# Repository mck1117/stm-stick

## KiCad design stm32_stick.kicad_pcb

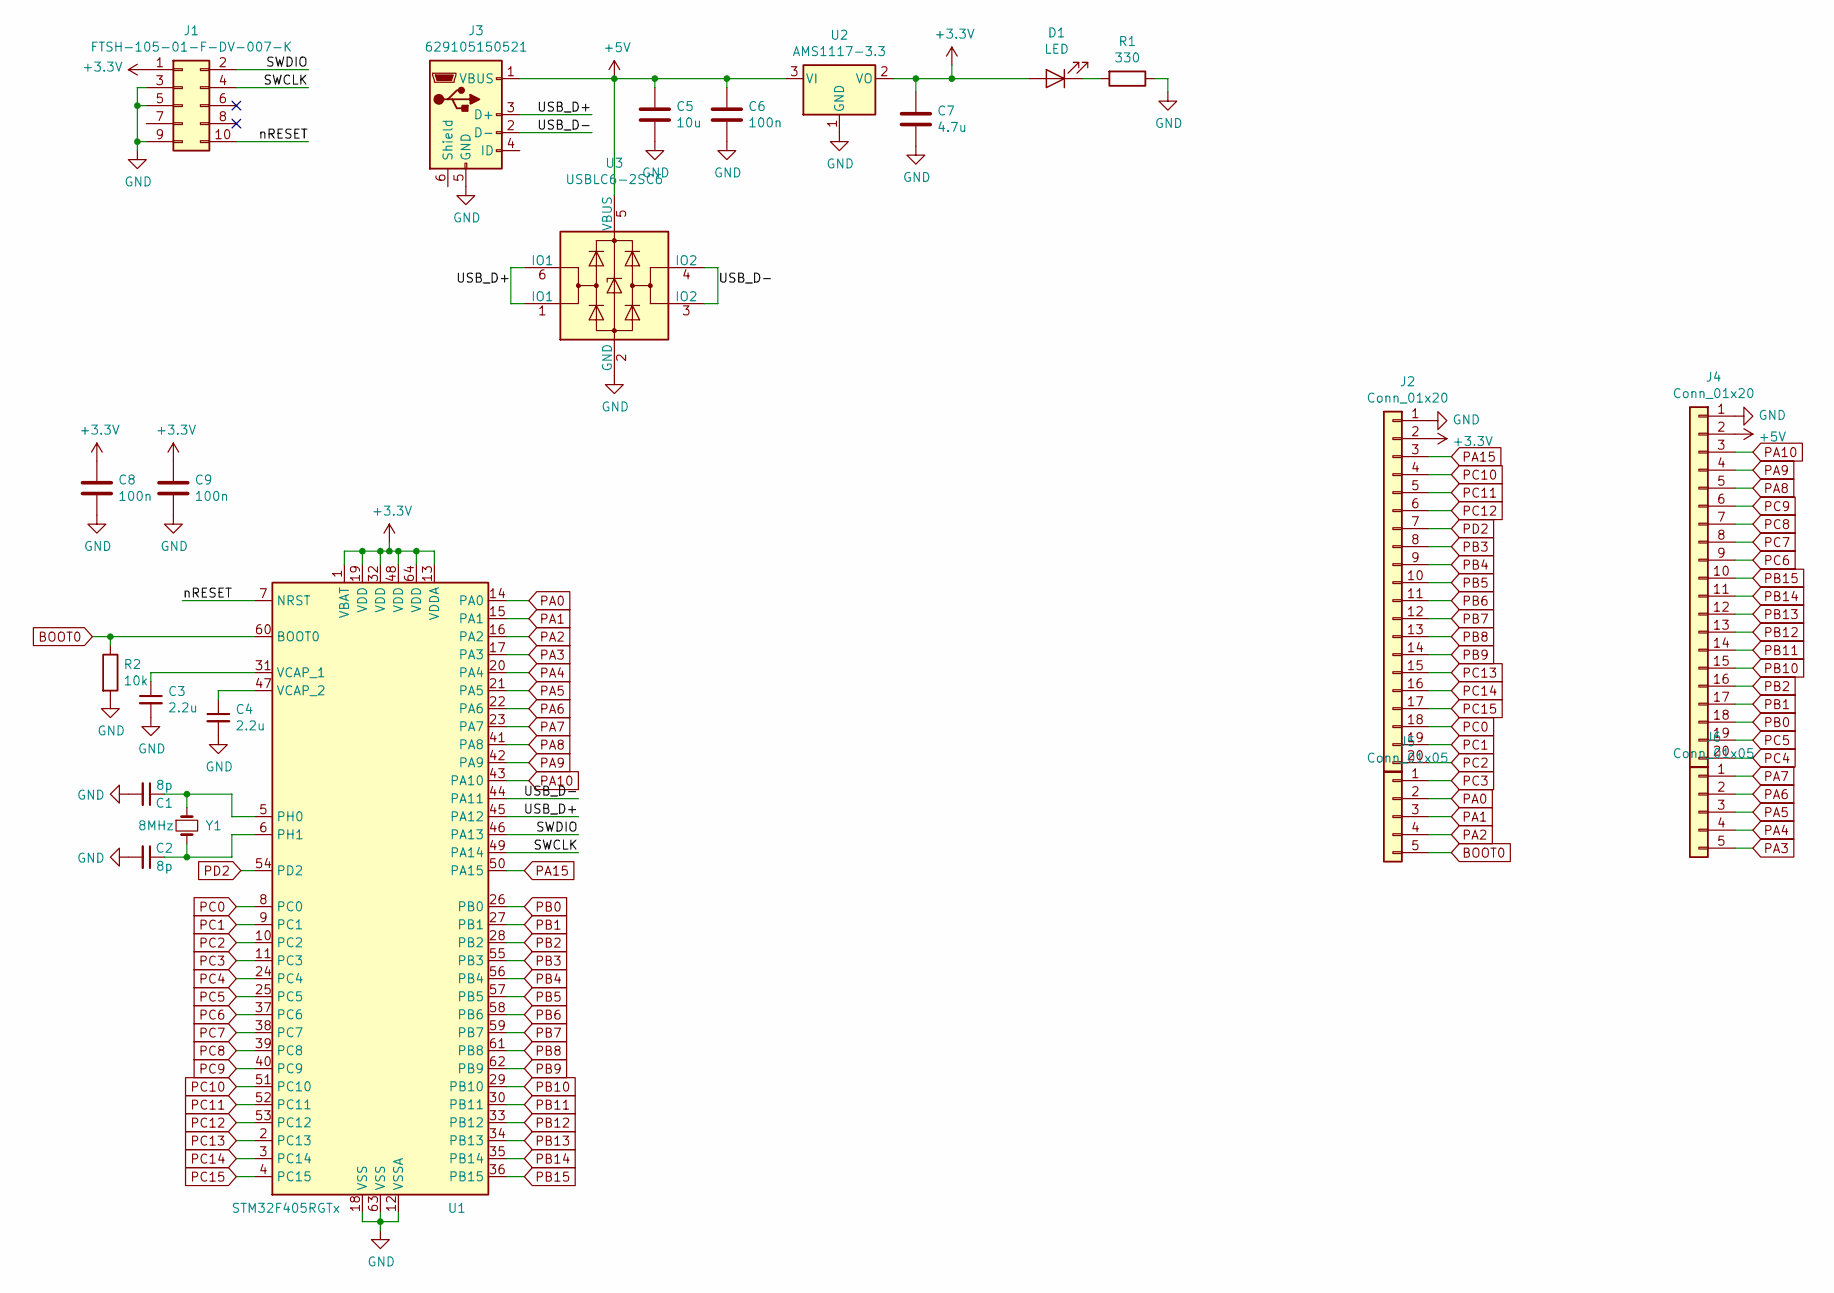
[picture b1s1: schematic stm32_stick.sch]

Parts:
C1, C2: 8p; C_0402_1005Metric; LCSC C1562
C3, C4: 2.2u; C_0603_1608Metric; LCSC C23630
C5: 10u; C_0603_1608Metric; LCSC C19702
C6, C8, C9: 100n; C_0402_1005Metric; LCSC C1525
C7: 4.7u; C_0603_1608Metric; LCSC C19666
D1: LED; LED_0603_1608Metric; LCSC C72038
J1: FTSH-105-01-F-DV-007-K; PinHeader_2x05_P1.27mm_Vertical_SMD; LCSC N/A
J2, J4: Conn_01x20; PinHeader_1x20_P2.54mm_Vertical; LCSC N/A
J3: 629105150521; USB_Micro-B_Wuerth_629105150521; LCSC N/A
J5, J6: Conn_01x05; PinHeader_1x05_P2.54mm_Vertical; LCSC N/A
R1: 330; R_0402_1005Metric; LCSC C25104
R2: 10k; R_0402_1005Metric; LCSC C25744
U1: STM32F405RGTx; LQFP-64_10x10mm_P0.5mm; LCSC C15742
U2: AMS1117-3.3; SOT-223-3_TabPin2; LCSC C6186
U3: USBLC6-2SC6; SOT-23-6
Y1: 8MHz; Crystal_SMD_5032-2Pin_5.0x3.2mm; LCSC C115962

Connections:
+3V3: C7.1, C8.1, C9.1, D1.2 (A), J1.1, J2.2, U1.1 (VBAT), U1.13 (VDDA), U1.19 (VDD), U1.32 (VDD), U1.48 (VDD), U1.64 (VDD), U2.2 (VO)
+5V: C5.1, C6.1, J3.1 (VBUS), J4.2, U2.3 (VI), U3.5 (VBUS)
/SWCLK: J1.4, U1.49 (PA14)
/SWDIO: J1.2, U1.46 (PA13)
/USB_D+: J3.3 (D+), U1.45 (PA12), U3.1 (IO1), U3.6 (IO1)
/USB_D-: J3.2 (D-), U1.44 (PA11), U3.3 (IO2), U3.4 (IO2)
/nRESET: J1.10, U1.7 (NRST)
BOOT0: J5.5, R2.1, U1.60 (BOOT0)
GND: C1.2, C2.2, C3.2, C4.2, C5.2, C6.2, C7.2, C8.2, C9.2, J1.3, J1.5, J1.9, J2.1, J3.5 (GND), J4.1, R1.1, R2.2, U1.12 (VSSA), U1.18 (VSS), U1.63 (VSS), U2.1 (GND), U3.2 (GND)
unnamed: C1.1, U1.5 (PH0), Y1.1
unnamed: C2.1, U1.6 (PH1), Y1.2
unnamed: C3.1, U1.31 (VCAP_1)
unnamed: C4.1, U1.47 (VCAP_2)
unnamed: D1.1 (K), R1.2
PA0: J5.2, U1.14 (PA0)
PA1: J5.3, U1.15 (PA1)
PA2: J5.4, U1.16 (PA2)
PA3: J6.5, U1.17 (PA3)
PA4: J6.4, U1.20 (PA4)
PA5: J6.3, U1.21 (PA5)
PA6: J6.2, U1.22 (PA6)
PA7: J6.1, U1.23 (PA7)
PA8: J4.5, U1.41 (PA8)
PA9: J4.4, U1.42 (PA9)
PA10: J4.3, U1.43 (PA10)
PA15: J2.3, U1.50 (PA15)
PB0: J4.18, U1.26 (PB0)
PB1: J4.17, U1.27 (PB1)
PB2: J4.16, U1.28 (PB2)
PB3: J2.8, U1.55 (PB3)
PB4: J2.9, U1.56 (PB4)
PB5: J2.10, U1.57 (PB5)
PB6: J2.11, U1.58 (PB6)
PB7: J2.12, U1.59 (PB7)
PB8: J2.13, U1.61 (PB8)
PB9: J2.14, U1.62 (PB9)
PB10: J4.15, U1.29 (PB10)
PB11: J4.14, U1.30 (PB11)
PB12: J4.13, U1.33 (PB12)
PB13: J4.12, U1.34 (PB13)
PB14: J4.11, U1.35 (PB14)
PB15: J4.10, U1.36 (PB15)
PC0: J2.18, U1.8 (PC0)
PC1: J2.19, U1.9 (PC1)
PC2: J2.20, U1.10 (PC2)
PC3: J5.1, U1.11 (PC3)
PC4: J4.20, U1.24 (PC4)
PC5: J4.19, U1.25 (PC5)
PC6: J4.9, U1.37 (PC6)
PC7: J4.8, U1.38 (PC7)
PC8: J4.7, U1.39 (PC8)
PC9: J4.6, U1.40 (PC9)
PC10: J2.4, U1.51 (PC10)
PC11: J2.5, U1.52 (PC11)
PC12: J2.6, U1.53 (PC12)
PC13: J2.15, U1.2 (PC13)
PC14: J2.16, U1.3 (PC14)
PC15: J2.17, U1.4 (PC15)
PD2: J2.7, U1.54 (PD2)

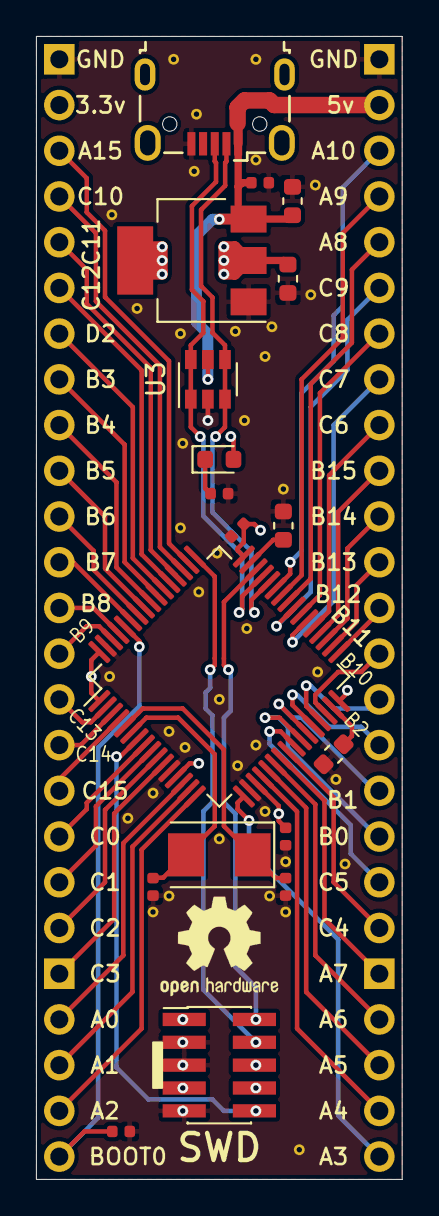
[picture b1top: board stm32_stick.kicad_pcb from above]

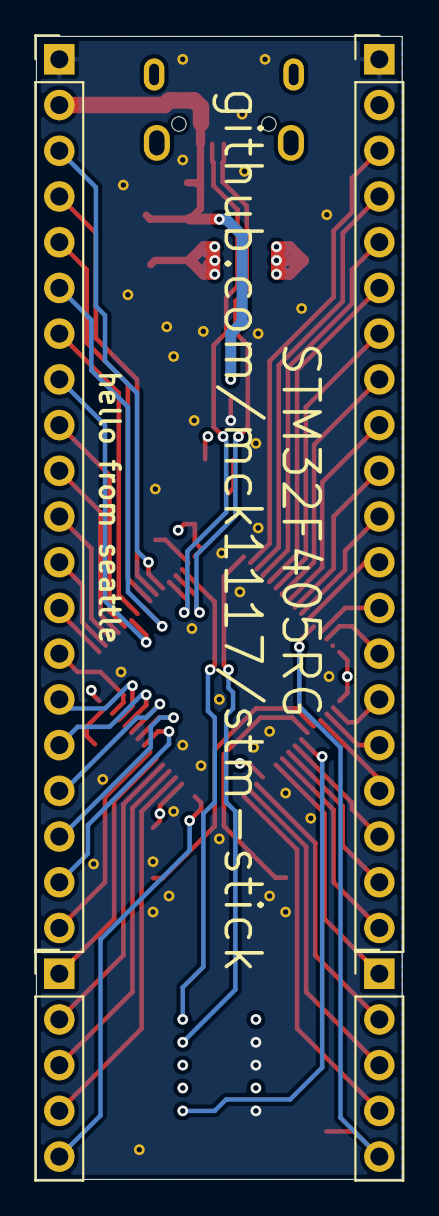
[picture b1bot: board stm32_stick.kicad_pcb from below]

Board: 4 copper layers, 20.3 x 63.5 mm, 22 parts (4 on the bottom side), 59 nets.

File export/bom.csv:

Comment,Designator,Footprint, LCSC
8p,"C1,C2",Capacitor_SMD:C_0402_1005Metric,C1562
2.2u,"C4,C3",Capacitor_SMD:C_0603_1608Metric,C23630
10u,C5,Capacitor_SMD:C_0603_1608Metric,C19702
100n,"C6,C8,C9",Capacitor_SMD:C_0402_1005Metric,C1525
4.7u,C7,Capacitor_SMD:C_0603_1608Metric,C19666
LED,D1,LED_SMD:LED_0603_1608Metric,C72038
FTSH-105-01-F-DV-007-K,J1,Connector_PinHeader_1.27mm:PinHeader_2x05_P1.27mm_Vertical_SMD,N/A
Conn_01x20,"J2,J4",Connector_PinHeader_2.54mm:PinHeader_1x20_P2.54mm_Vertical,N/A
6.29105E+11,J3,Connector_USB:USB_Micro-B_Wuerth_629105150521,N/A
Conn_01x05,"J5,J6",Connector_PinHeader_2.54mm:PinHeader_1x05_P2.54mm_Vertical,N/A
330,R1,Resistor_SMD:R_0402_1005Metric,C25104
10k,R2,Resistor_SMD:R_0402_1005Metric,C25744
STM32F405RGTx,U1,Package_QFP:LQFP-64_10x10mm_P0.5mm,C15742
AMS1117-3.3,U2,Package_TO_SOT_SMD:SOT-223-3_TabPin2,C6186
USBLC6-2SC6,U3,Package_TO_SOT_SMD:SOT-23-6,
8MHz,Y1,Crystal:Crystal_SMD_5032-2Pin_5.0x3.2mm,C115962

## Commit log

2020-09-08 gitignore
2020-09-08 boot0 resistro
2020-09-08 note
2020-10-14 don't ignore csv
2020-10-27 production outputs
